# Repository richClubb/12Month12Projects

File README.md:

# 12Month12Projects
This repository contains 12 projects in 12 months.

The aim of this task is to create 12 distinct projects in 12 months. Each project should be scoped to be able to be delivered and completed by the end of the month. It might be that different months build on a previous month project, but the project must be completed by the last day of the month. This is to enforce scoping and avoid scope creep.

Each project will be detailed in their own folder and on their own wiki Page

## Rules
1. Each project WILL take 1 month - If the project is not finished in the month then it can be revisited later, but it should be a secondary priority. The whole objective is to deliver and finish the project in 1 month, and if this is not possible then the project has not necessarily failed, but it needs to be tied off
2. Do not start work on another project until the start date - If you are working on a project do not start on another. It's fine to have ideas for new projects, but it should not go past the concept phase.

## Projects

1. [Month 01 - Raspi-door-camera](https://github.com/richClubb/12Month12Projects/wiki/Month-01---Raspi-Front-Door-Camera) - A standalong front door camera and experiments with setting up video pipelines

## Archive

I ran this project in 2019 and failed after the first 2 months due to a couple of factors, but the first two projects were interesting. They can be found in the Archive folder

[Month 1 - Usb To Serial PCB](https://github.com/richClubb/12Month12Projects/wiki/Month-01-Usb-To-Serial-PCB) - Put in correct links

[Month 2 - Self Balancing Robot](https://github.com/richClubb/12Month12Projects/wiki/Month-02-Self-Balancing-Robot) - Put in correct links

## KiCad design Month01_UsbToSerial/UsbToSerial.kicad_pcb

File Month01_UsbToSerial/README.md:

# Month 1 - UsbToSerial

## Brief

Create a single layer USB to Serial board based around the FTDI FT232RL chip.

A few years ago I made a stripboard arduino, but one key component that was missing was a USB to serial converter for programming. I bought a sparkfun FTDI breakout board, but it was around £12. It was very good and compact but I thought it was quite expensive as the entire stripboard was less than £10

I thought it would be good to try and create a board that could be created at home or with very simple tools.

## Objectives

### Primary

1. Create a single layer layout for the FT232RL chip
1. Make it possible to create in a standard hackspace
1. Make it less than £10 to fabricate and populate
1. Make the interface work with standard stripboard 2.54 mm pitch

### Secondary

1. Actually make the PCB

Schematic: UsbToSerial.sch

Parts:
C1: 100nf; C_0603_1608Metric
C2: 100nF; C_0603_1608Metric
C3: 10uF; CP_Elec_3x5.3
D1: PWR_LED; LED_1206_3216Metric
D2: TX_LED; LED_1206_3216Metric
D3: RX_LED; LED_1206_3216Metric
J1: USB_B_Micro; USB_Micro-B_GCT_USB3076-30-A
J2, J3: Conn_01x08_Male; PinHeader_1x08_P2.54mm_Vertical
JP1: PowerSelect; PinHeader_1x03_P2.54mm_Vertical
R1: RX_R; R_0603_1608Metric
R2: TX_R; R_0603_1608Metric
R3: R_Small; R_0603_1608Metric
U1: FT232RL; SSOP-28_5.3x10.2mm_P0.65mm

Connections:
+3V3: C1.1, JP1.3 (B), U1.17 (3V3OUT)
+5V: C2.1, C3.1, J1.1 (VBUS), JP1.1 (A), R3.1, U1.20 (VCC)
CTS: J3.1, U1.11 (CTS)
DCD: J3.2, U1.10 (DCD)
DCR: J3.3, U1.9 (DCR)
DTR: J2.6, J3.4, U1.2 (DTR)
GNDREF: C1.2, C2.2, C3.2, D1.1 (K), J1.5 (GND), J2.1, J2.3, J3.8, U1.7 (GND), U1.18 (GND), U1.21 (GND), U1.25 (AGND), U1.26 (TEST)
unnamed: D1.2 (A), R3.2
unnamed: D2.1 (K), U1.23 (CBUS0)
unnamed: D2.2 (A), R2.1
unnamed: D3.1 (K), U1.22 (CBUS1)
unnamed: D3.2 (A), R1.1
unnamed: J1.2 (D-), U1.16 (USBD-)
unnamed: J1.3 (D+), U1.15 (USBD+)
PWR: J2.2, J3.6, JP1.2 (C), R1.2, R2.2, U1.4 (VCCIO), U1.19 (~RESET~)
RTS: J2.5, U1.3 (RTS)
RXI: J2.8, J3.5, U1.5 (RXD)
TX0: J2.7, J3.7, U1.1 (TXD)

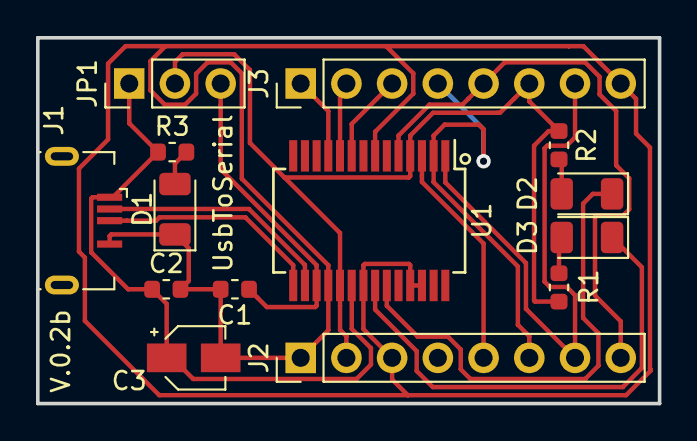
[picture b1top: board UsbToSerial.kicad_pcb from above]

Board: 2 copper layers, 34.5 x 20.3 mm, 14 parts (0 on the bottom side), 18 nets.

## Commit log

2019-07-08 Update README.md
    Initial commit for month 1 and month 2
2019-07-08 commit of initial schematic and PCB layout
2019-07-08 month 1 readme
2019-07-13 added files from mistaken working copy in separate folder
2019-07-13 Changed readme for general proejct and the Month01 project
2019-07-14 Deleted mistakenly committed files and added more detail to the month1 readme
2019-07-15 Corrected position of the headers as I misplaced the connector
2019-07-15 Updated README.md
    added more content to the readme, and a Things to Learn from
2019-07-15 updated usbtoSerial.kicad_pcb with corrected layout
2019-07-17 Updated main redme for month3 project
2019-07-17 Slight modification to PCB layout, added more to month1 readme
2019-07-17 minor update to main readme.md
2019-07-23 Added a new idea for later months of the project
2019-07-23 Added section for the rules of the exercise
2019-07-23 Minor addition to readme
2019-07-23 Added Month02 initial data
2019-07-24 Added log entry
2019-07-24 Added images folder with an image of the board
2019-07-24 Added image to readme
2019-07-24 added small details
    added extra entries to Things to learn from, added image of PCB
2019-07-25 Added version number to board
2019-07-25 Added new layout with reduced footprint
2019-07-25 Minor modification to V0.2b
2019-07-26 minor mod to correct spacing
2019-07-26 added extra text to the bottom layer of the board, changed pin headers to 8 instead of 7
2019-07-26 Added v_0_2b files
2019-07-26 Added a little extra items to the outcomes
2019-07-26 Month 01 - Added extra info to the README for the final points, added extra images
2019-07-26 Accidentally committed PCB before saving the working copy
2019-07-26 Minor correction
2019-07-26 Added extra detail to Project Finish section
2019-07-27 Minor modification to the board and schematic to utilise unused pins, deleted old files
2019-07-27 added gerber outputs and minor mod to PCB
2019-07-27 added zip of the gerber outputs
2019-07-27 changed general 3d images and added 1 more
2019-07-27 Update to main README after Month 01 completion
2019-07-27 Minor mod to main README
2019-07-27 Minor mod to readme for month02
2019-07-27 #1 test
2019-07-27 Added note to readme for month 02
2019-07-29 Addition to notes on Desk Inspection lamp idea
2019-07-29 #3 added via and track to back of board for DTR pin
2019-07-30 Minor changes to fix broken link reference
2019-07-30 Addition to primary and secondary objectives
2019-08-05 Removed month notes to put into wiki
2019-08-05 Modified main readme to be clearer
2019-08-05 Moved details to wiki
2019-08-06 Added base code for month 02, added month 03 readme
2019-08-06 added basic code to perform movement, but it is very basic and the integral term is not correct
2019-09-01 modifications to code for Month02 robot
2019-09-01 added images for the project documentation
2020-05-26 added Month04
2020-05-26 Test commit
2021-02-03 Started again, shifted the 2 completed projects into the archive as I don't want to lose them completley
2021-02-08 notes on test setups
2021-02-08 Moved files
2021-02-08 Update generalnotes.md
    added source command
2021-02-08 Update generalnotes.md
    Added note to figure out h264 encoding / decoding
2021-03-10 Added images for dovetail box
2021-03-11 Added design for the spice box
2021-03-11 Added box design
